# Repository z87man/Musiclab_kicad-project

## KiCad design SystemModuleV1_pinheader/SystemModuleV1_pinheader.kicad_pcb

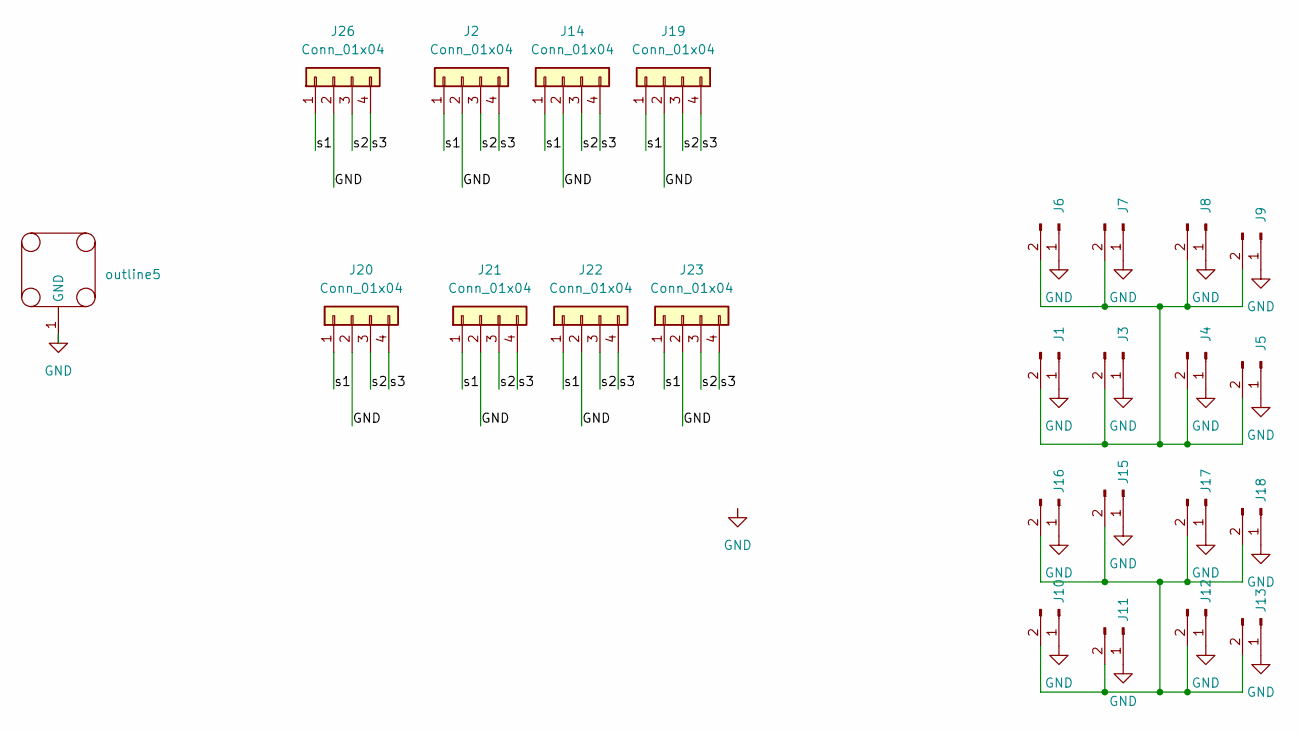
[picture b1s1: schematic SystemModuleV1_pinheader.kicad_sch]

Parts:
J1, J3, J4, J5, J6, J7, J8, J9, J10, J11, J12, J13, J15, J16, J17, J18: Conn_01x02_Pin; PinHeader_1x02_P2.54mm_Vertical_SMD_Pin1Left
J2, J14, J19, J20, J21, J22, J23, J26: Conn_01x04; PinHeader_1x04_P2.54mm_Vertical_SMD_Pin1Left
outline5: Outline_sys3x3_cavity_1.5mm

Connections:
/s1: J2.1, J14.1, J19.1, J20.1, J21.1, J22.1, J23.1, J26.1
/s2: J2.3, J14.3, J19.3, J20.3, J21.3, J22.3, J23.3, J26.3
/s3: J2.4, J14.4, J19.4, J20.4, J21.4, J22.4, J23.4, J26.4
GND: J1.1, J2.2, J3.1, J4.1, J5.1, J6.1, J7.1, J8.1, J9.1, J10.1, J11.1, J12.1, J13.1, J14.2, J15.1, J16.1, J17.1, J18.1, J19.2, J20.2, J21.2, J22.2, J23.2, J26.2, outline5.1 (GND)
unnamed: J1.2, J3.2, J4.2, J5.2, J6.2, J7.2, J8.2, J9.2
unnamed: J10.2, J11.2, J12.2, J13.2, J15.2, J16.2, J17.2, J18.2

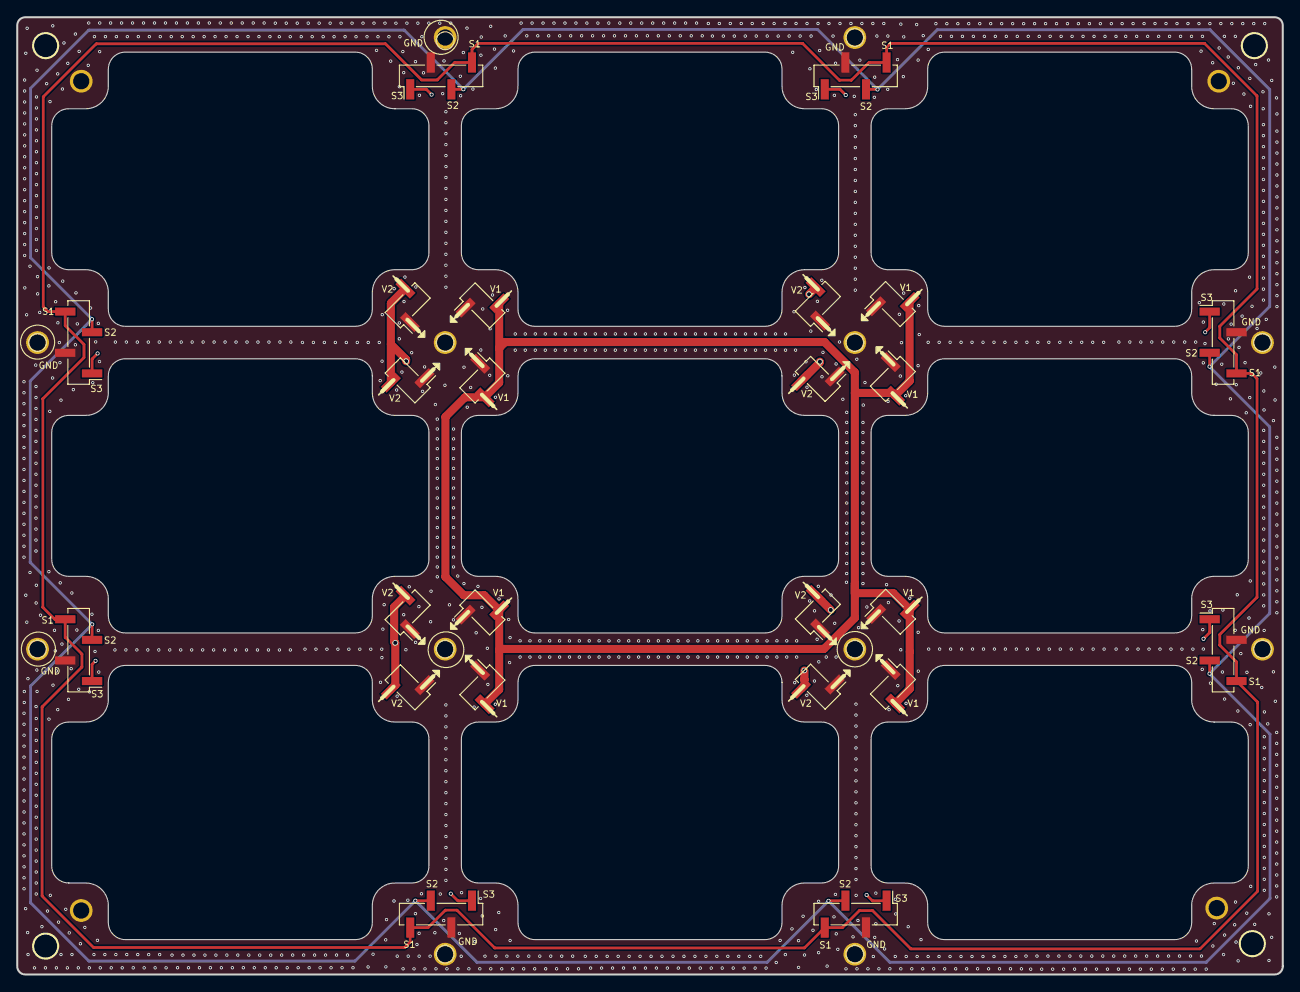
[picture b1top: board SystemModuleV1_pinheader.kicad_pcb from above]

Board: 4 copper layers, 156.0 x 118.0 mm, 25 parts (0 on the bottom side), 6 nets.

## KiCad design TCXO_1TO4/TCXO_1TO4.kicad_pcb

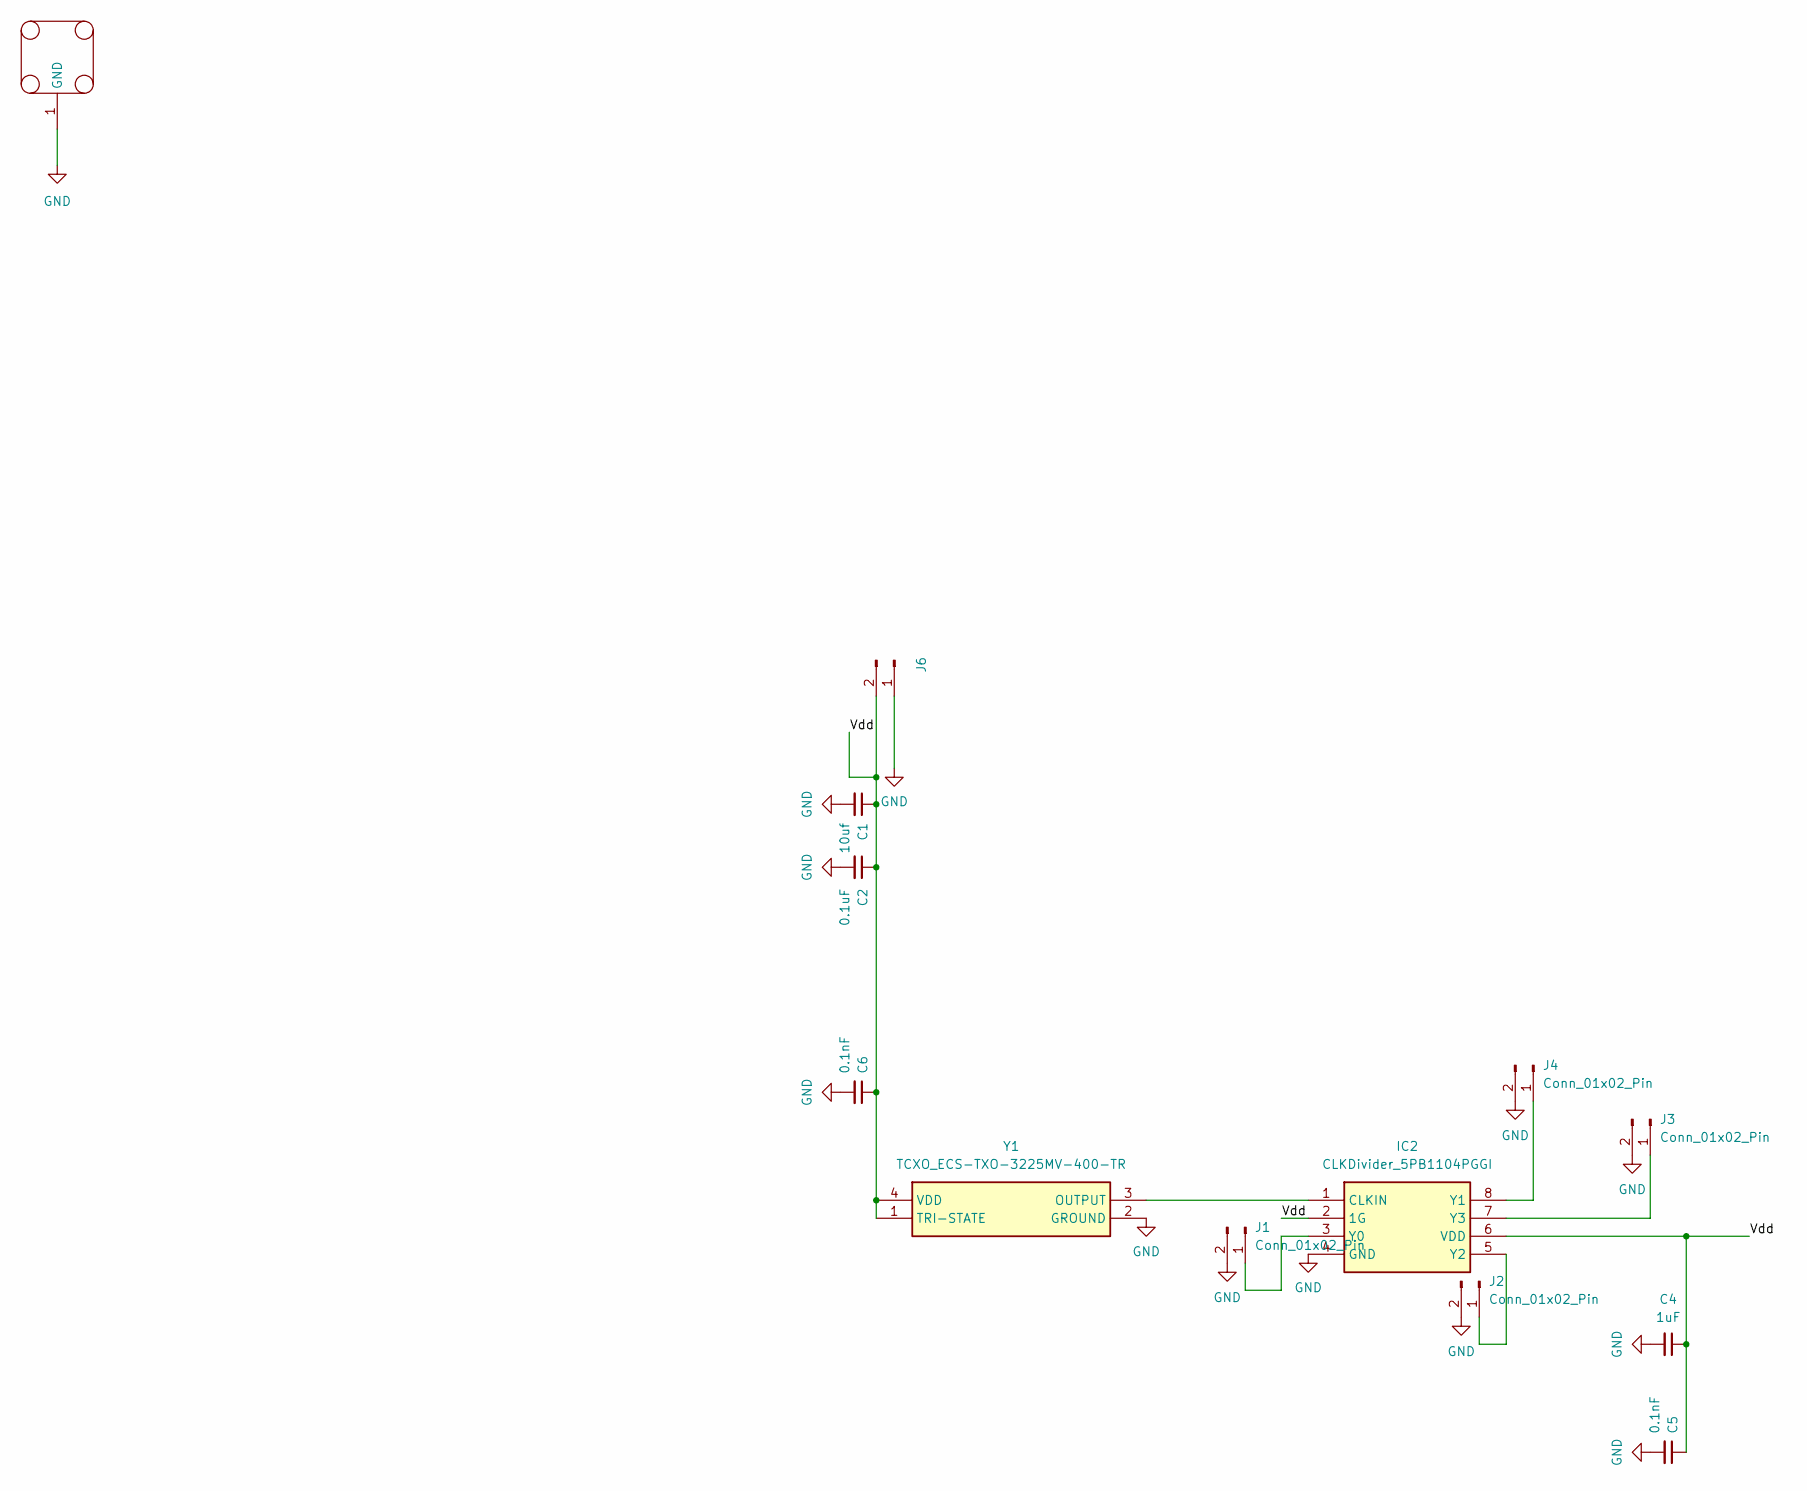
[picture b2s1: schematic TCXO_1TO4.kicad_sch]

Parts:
C1: 10uf; C_0603_1608Metric
C2: 0.1uF; C_0603_1608Metric
C4: 1uF; C_0603_1608Metric
C5, C6: 0.1nF; C_0603_1608Metric
IC2: CLKDivider_5PB1104PGGI; CLKDivider_SOP65P640X120-8N; Mouser Part Number 972-5PB1104PGGI
J1: Conn_01x02_Pin; PinHeader_1x02_P2.54mm_Vertical
J2, J3, J4: Conn_01x02_Pin; SMA_KHD_Back
J6: Conn_01x02_Pin; JST_XH_B2B-XH-A_1x02_P2.50mm_Vertical
Y1: TCXO_ECS-TXO-3225MV-400-TR; TXCO_ECSTXO3225MV400TR; Mouser Part Number 520-TXO-3225MV-400TR
outline1: Outline_3x2_cavity_20231207

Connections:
/Vdd: C1.1, C2.1, C4.1, C5.1, C6.1, IC2.2 (1G), IC2.6 (VDD), J6.2, Y1.1 (TRI-STATE), Y1.4 (VDD)
GND: C1.2, C2.2, C4.2, C5.2, C6.2, IC2.4 (GND), J1.2, J2.2, J3.2, J4.2, J6.1, Y1.2 (GROUND), outline1.1 (GND)
unnamed: IC2.1 (CLKIN), Y1.3 (OUTPUT)
unnamed: IC2.3 (Y0), J1.1
unnamed: IC2.8 (Y1), J4.1
unnamed: IC2.5 (Y2), J2.1
unnamed: IC2.7 (Y3), J3.1

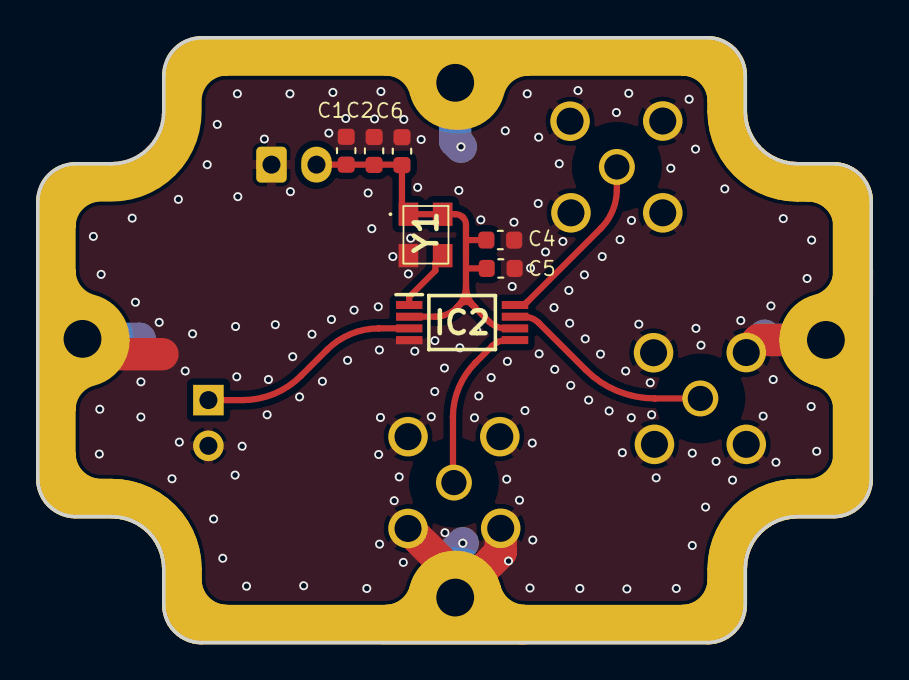
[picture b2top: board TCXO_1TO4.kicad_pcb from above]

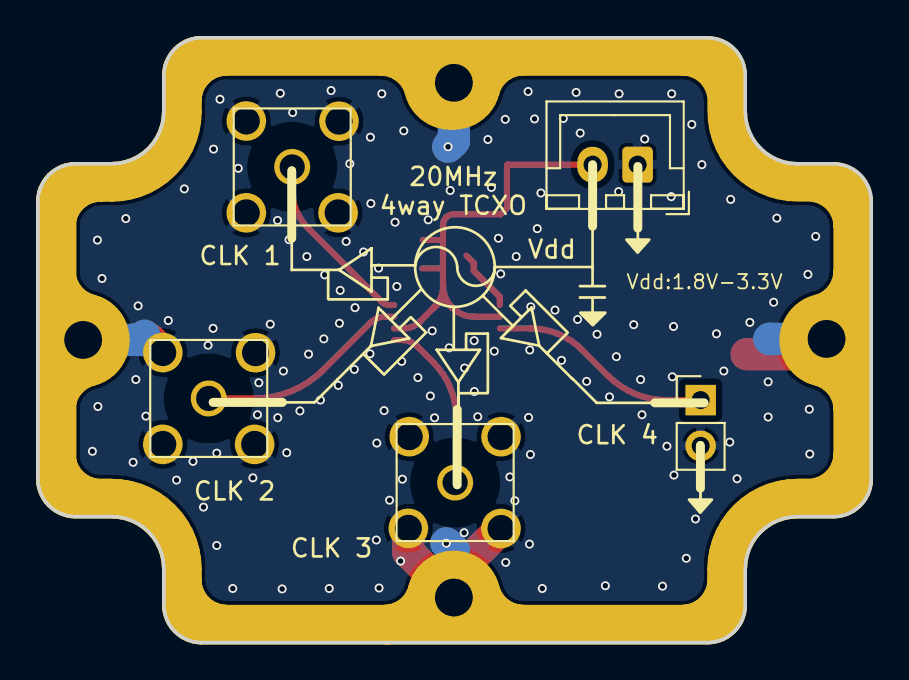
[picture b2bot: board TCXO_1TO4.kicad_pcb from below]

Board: 4 copper layers, 46.3 x 33.6 mm, 13 parts (5 on the bottom side), 7 nets.

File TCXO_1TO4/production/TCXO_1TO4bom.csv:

Designator,Footprint,Quantity,Value,LCSC Part #
C1,0603,1,10uf,
C2,0603,1,0.1uF,
C4,0603,1,1uF,
"C5, C6",0603,2,0.1nF,
IC2,CLKDivider_SOP65P640X120-8N,1,CLKDivider_5PB1104PGGI,
J1,PinHeader_1x02_P2.54mm_Vertical,1,Conn_01x02_Pin,
"J2, J3, J4",SMA_KHD_Back,3,Conn_01x02_Pin,
J6,JST_XH_B2B-XH-A_1x02_P2.50mm_Vertical,1,Conn_01x02_Pin,
Y1,TXCO_ECSTXO3225MV400TR,1,TCXO_ECS-TXO-3225MV-400-TR,
outline1,Outline_3x2_cavity_20231207,1,~,

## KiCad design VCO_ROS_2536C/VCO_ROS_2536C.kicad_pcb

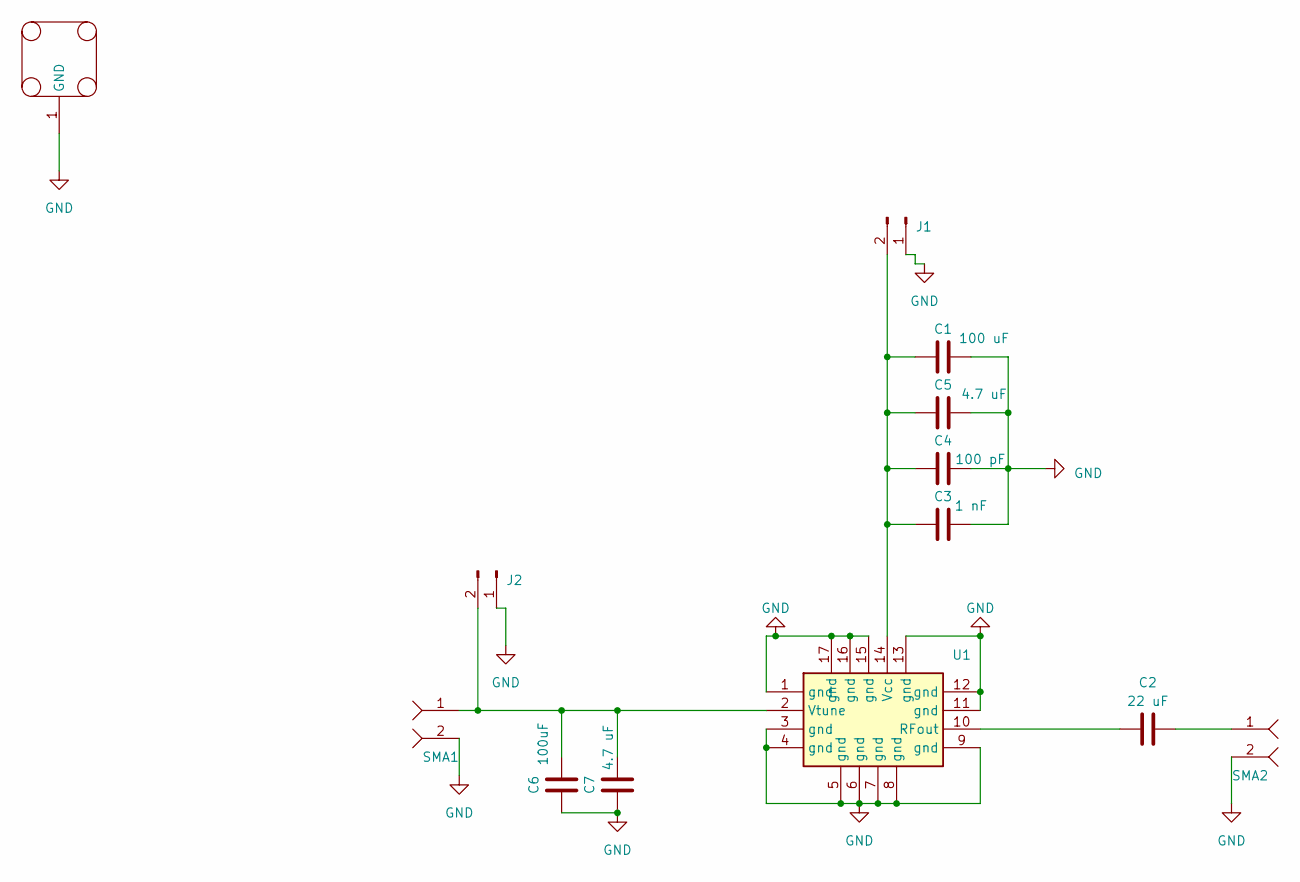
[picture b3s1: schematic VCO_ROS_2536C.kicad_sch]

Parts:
C1: 100 uF; C_0603_1608Metric
C2: 22 uF; C_0603_1608Metric
C3: 1 nF; C_0603_1608Metric
C4: 100 pF; C_0603_1608Metric
C5, C7: 4.7 uF; C_0603_1608Metric
C6: 100uF; C_0603_1608Metric
J1: Conn_01x02_Pin; JST_XH_B2B-XH-AM_1x02_P2.50mm_Vertical_changed
J2: Conn_01x02_Pin; PinHeader_1x02_P2.54mm_Vertical
SMA1, SMA2: SMA_KHD_Back
U1: VCO_CK1113
outline1: Outline_3x2_cavity_20231207

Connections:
GND: C1.2, C3.2, C4.2, C5.2, C6.1, C7.1, J1.1, J2.1, SMA1.2, SMA2.2, U1.1 (gnd), U1.3 (gnd), U1.4 (gnd), U1.5 (gnd), U1.6 (gnd), U1.7 (gnd), U1.8 (gnd), U1.9 (gnd), U1.11 (gnd), U1.12 (gnd), U1.13 (gnd), U1.15 (gnd), U1.16 (gnd), U1.17 (gnd), outline1.1 (GND)
unnamed: C2.2, SMA2.1
unnamed: C1.1, C3.1, C4.1, C5.1, J1.2, U1.14 (Vcc)
unnamed: C6.2, C7.2, J2.2, SMA1.1, U1.2 (Vtune)
unnamed: C2.1, U1.10 (RFout)

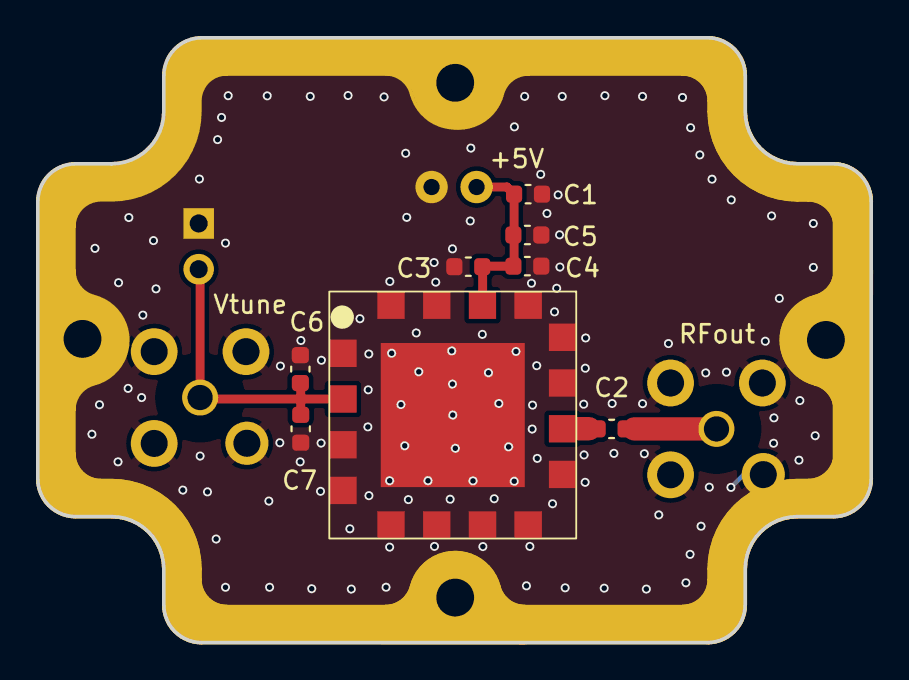
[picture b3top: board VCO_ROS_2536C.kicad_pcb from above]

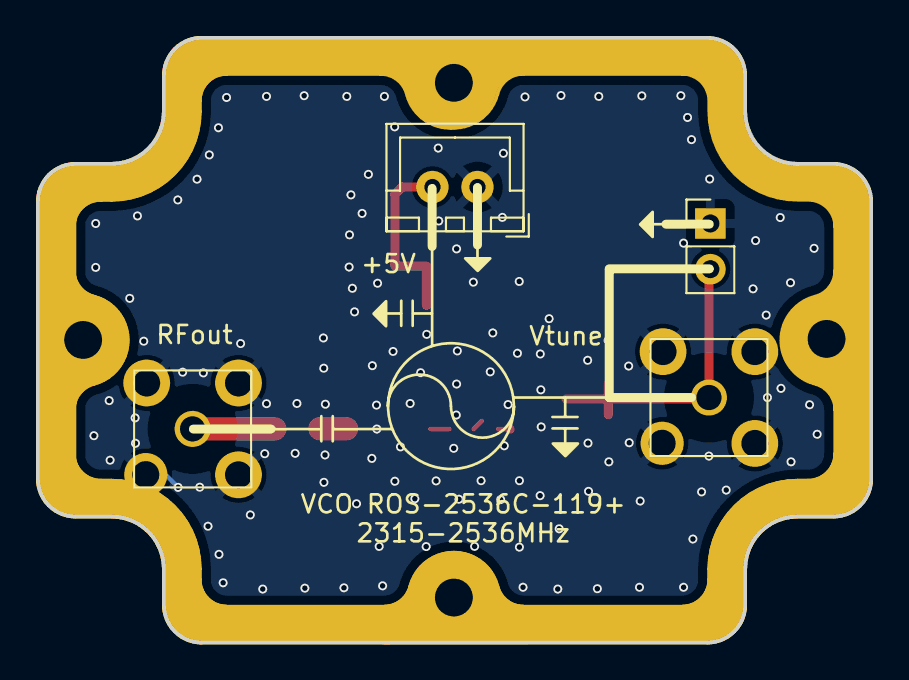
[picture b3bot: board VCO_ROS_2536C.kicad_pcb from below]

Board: 2 copper layers, 46.3 x 33.6 mm, 13 parts (4 on the bottom side), 5 nets.

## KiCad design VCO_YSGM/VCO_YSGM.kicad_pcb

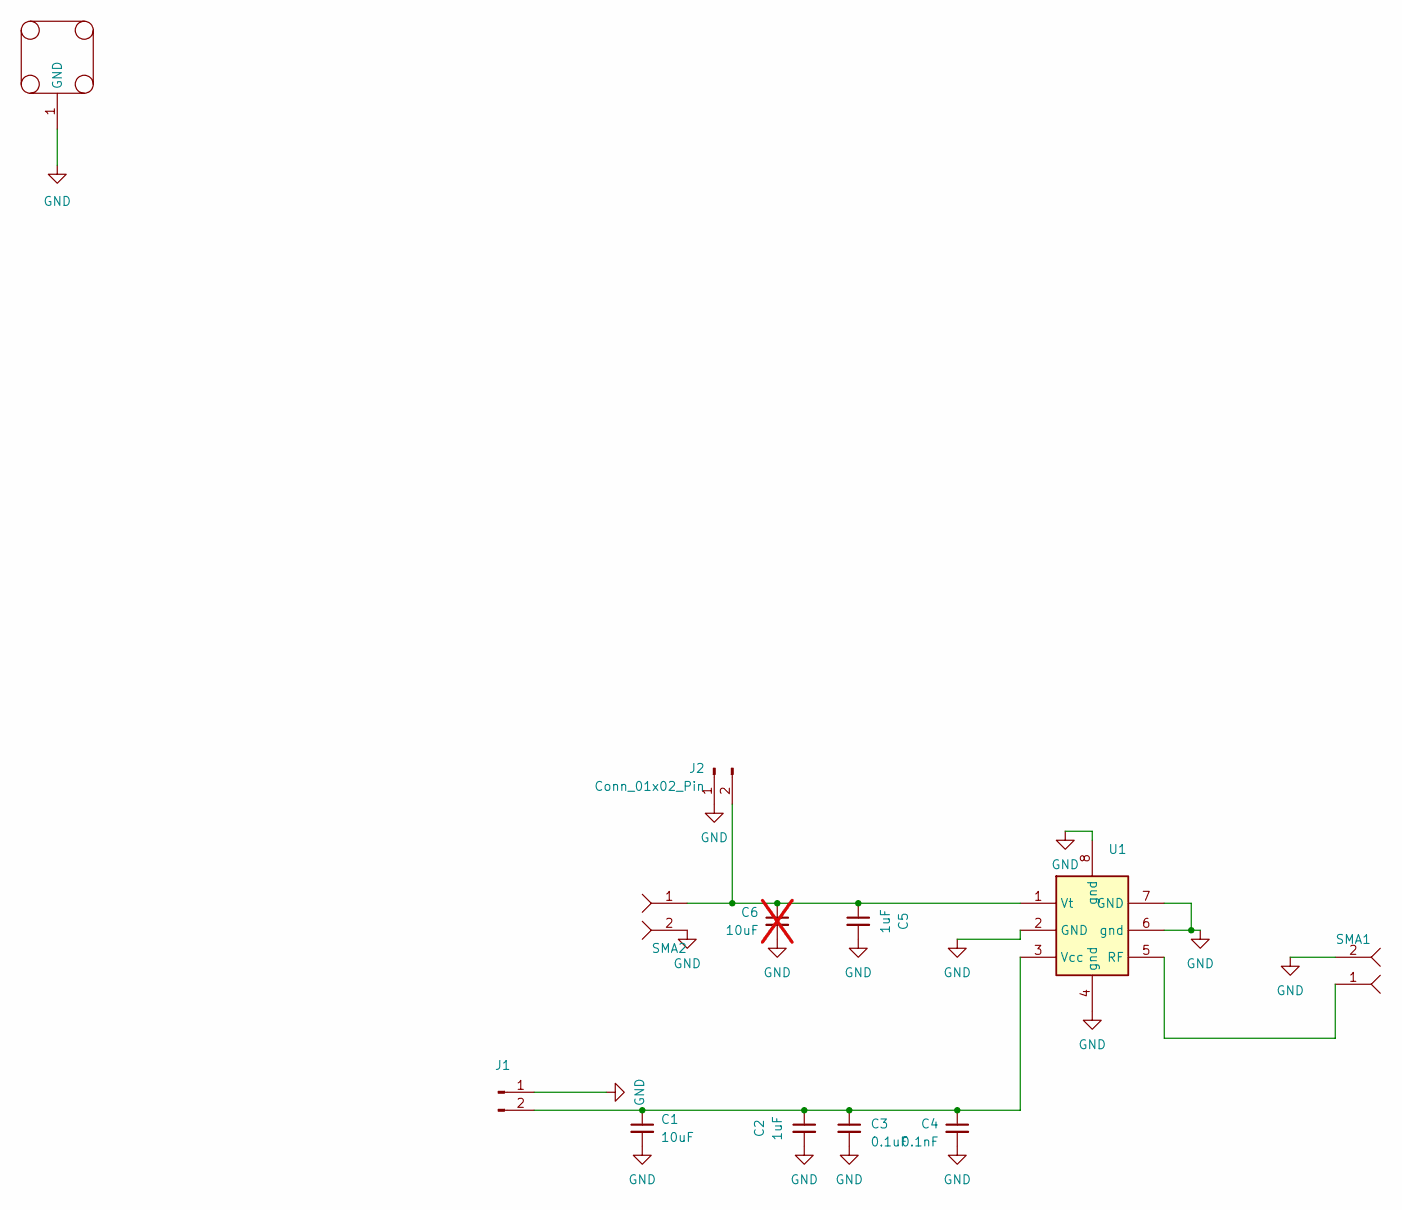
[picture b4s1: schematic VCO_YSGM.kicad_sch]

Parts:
C1: 10uF; C_0603_1608Metric
C2, C5: 1uF; C_0603_1608Metric
C3: 0.1uF; C_0603_1608Metric
C4: 0.1nF; C_0603_1608Metric
C6: 10uF; C_0603_1608Metric; not fitted
J1: Conn_01x02_Pin; JST_XH_B2B-XH-A_1x02_P2.50mm_Vertical
J2: Conn_01x02_Pin; PinHeader_1x02_P2.54mm_Vertical
SMA1, SMA2: SMA_KHD_Back
U1: VCO_ysgm
outline1: Outline_3x2_cavity_20231207

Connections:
GND: C1.2, C2.2, C3.2, C4.2, C5.2, C6.2, J1.1, J2.1, SMA1.2, SMA2.2, U1.2 (GND), U1.4 (gnd), U1.6 (gnd), U1.7 (GND), U1.8 (gnd), outline1.1 (GND)
unnamed: C1.1, C2.1, C3.1, C4.1, J1.2, U1.3 (Vcc)
unnamed: C5.1, C6.1, J2.2, SMA2.1, U1.1 (Vt)
unnamed: SMA1.1, U1.5 (RF)

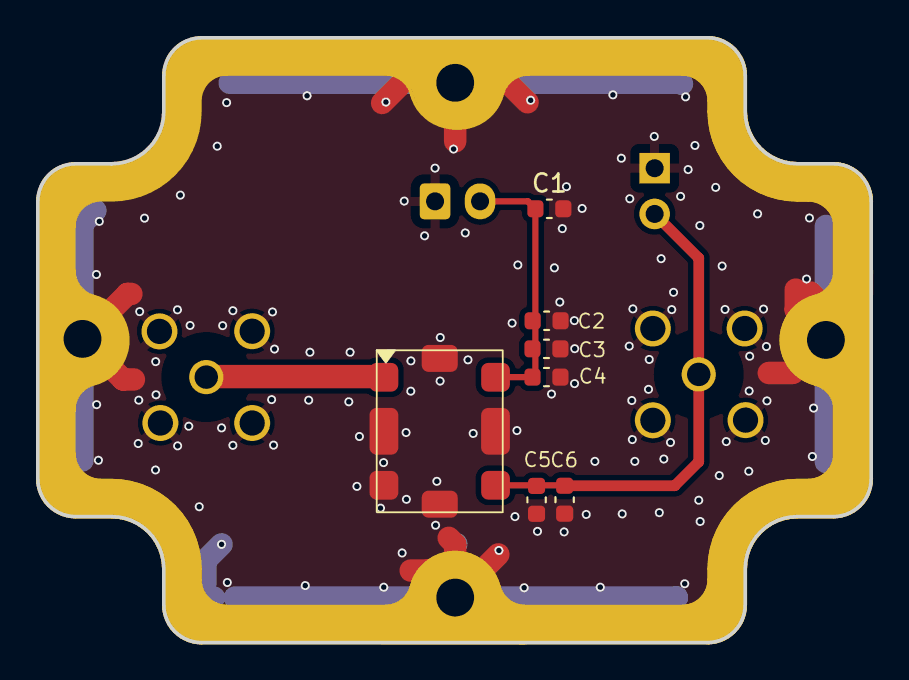
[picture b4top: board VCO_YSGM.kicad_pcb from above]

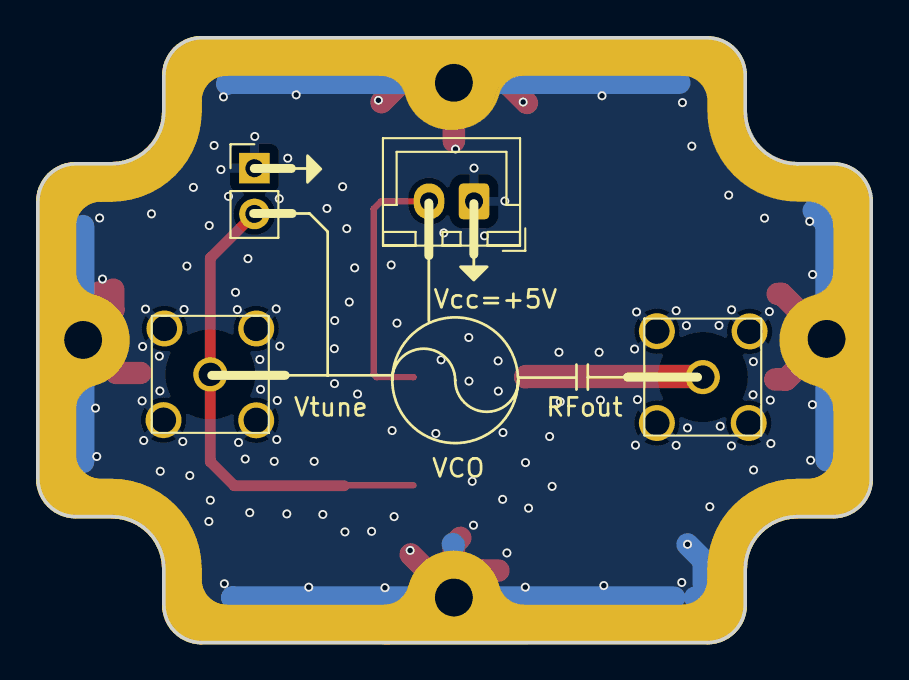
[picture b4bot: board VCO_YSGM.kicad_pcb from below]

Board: 2 copper layers, 46.3 x 33.6 mm, 12 parts (4 on the bottom side), 4 nets.
